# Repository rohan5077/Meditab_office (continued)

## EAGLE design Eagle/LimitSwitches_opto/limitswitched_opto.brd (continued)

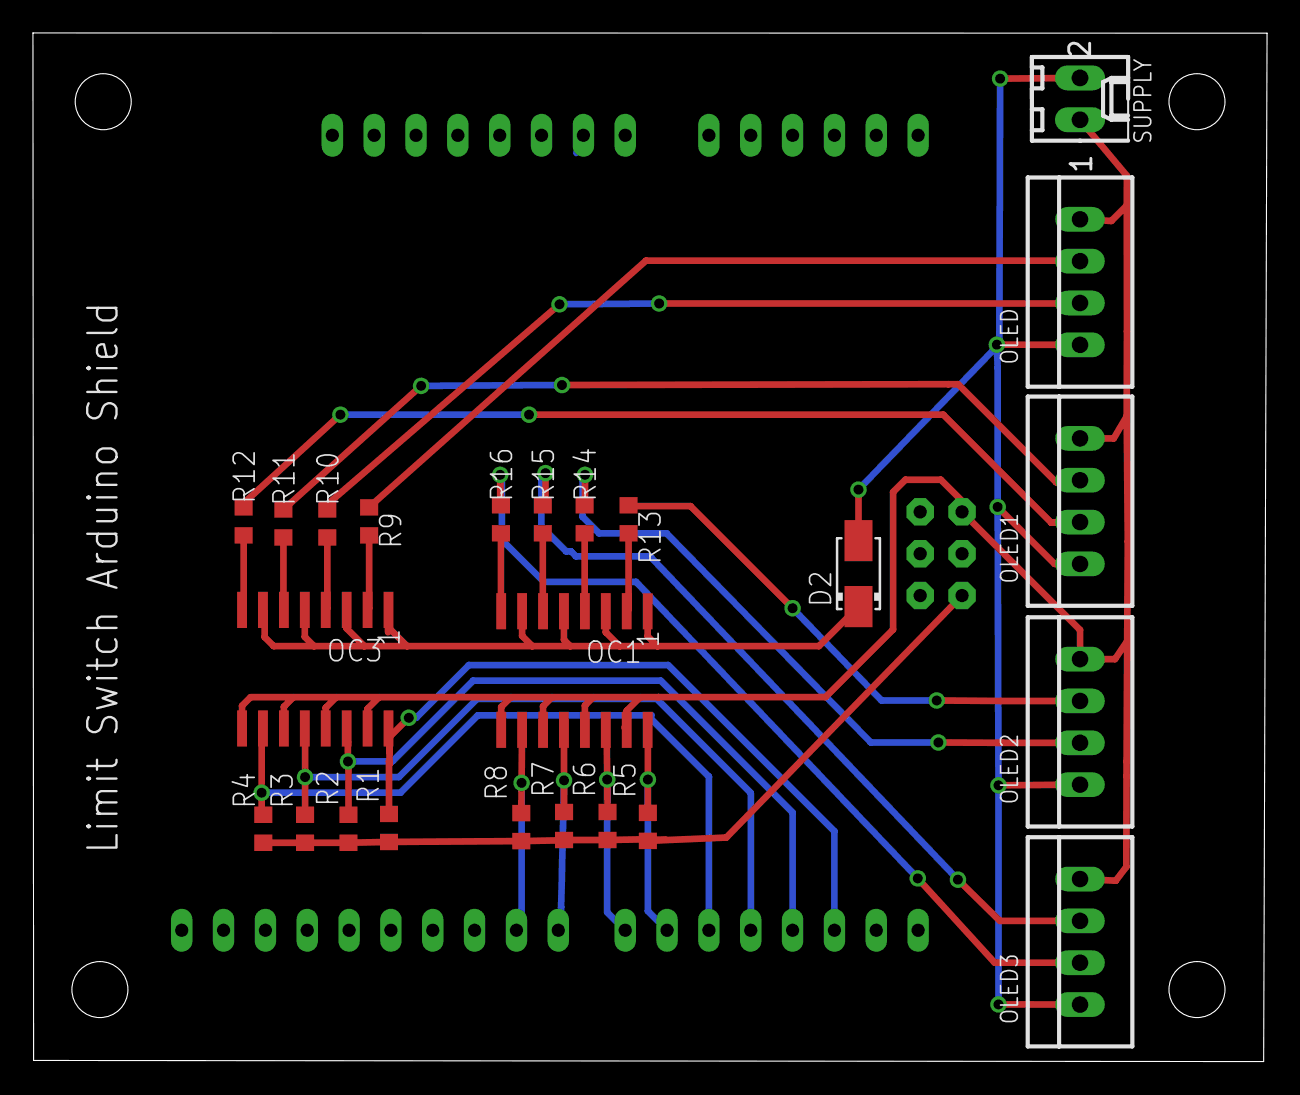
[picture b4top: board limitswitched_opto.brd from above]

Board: 2 copper layers, 74.9 x 62.4 mm, 25 parts (1 on the bottom side), 28 nets.
